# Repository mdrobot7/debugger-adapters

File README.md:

# debugger-adapters
Aliexpress STLINKv2 debugger to standard connector adapters

## Hardware
All part links are built into the KiCad parts, just generate the BOM from within KiCad and order. Miscellaneous parts are below.

- [Aliexpress STLINKv2](https://www.aliexpress.us/item/3256803389306042.html)
- [Cortex-debug Ribbon Cable](https://www.digikey.com/en/products/detail/cnc-tech/300-30-10-GR-0100F/5864892)
- [Pre-assembled Cortex-debug Cable](https://www.aliexpress.us/item/3256805917162371.html)

## Assembly
The ribbon cable IDC connectors for the Cortex-Debug adapter are quite difficult to get exactly right. If the wire goes in at slightly the wrong angle, the conductors will bridge or connect to the wrong pins. After each connector is put on, check each pin with a multimeter to make sure it's not bridged to anything it shouldn't be.

## Creating a Black Magic Probe
Black Magic Probe and Black Magic Debug are open-source SWD/JTAG debug projects for ARM Cortex microcontrollers. It gives you a bare GDB server and is platform-independent, so it will work on ARM Cortex microcontrollers regardless of brand or series.

To create a Black Magic Probe you need an existing debugger -- another Black Magic Probe, STLink (for ST-based debuggers), Atmel ICE (for Atmel chips), etc.

#### Resources
- [Black Magic Debug Website](https://black-magic.org/index.html)
- [Black Magic Debug Codeberg](https://codeberg.org/blackmagic-debug/blackmagic)
- [dfu-util Homepage](https://dfu-util.sourceforge.net/)
- [Zadig (Windows USB driver reinstaller)](https://zadig.akeo.ie/)

### Supported Hardware
- [Knockoff STLink v2 (Geehy MCU) - Aliexpress](https://www.aliexpress.us/item/3256803389306042.html)
- [Knockoff STLink v2 (STM32F101 MCU) - Aliexpress](https://www.aliexpress.us/item/3256803289344865.html)
- [STM32 "Blue Pill" (STM32F103C8T6) - Ebay](https://www.ebay.com/itm/292145343898)

### Wiring
Keep the SWD wires (between the BMP and the microcontroller) relatively short. SWD doesn't have a length spec, but under 30cm is a good rule of thumb. Slower baud rates will allow for longer lengths. It's recommended to extend the USB side instead of the SWD side.

### Reprogramming the BMP
The Black Magic Probe project switched to Meson in current releases, which makes installation a little harder on Windows. On Windows, your best move is load up a Linux VM using VirtualBox or something similar. You can try to get MSYS2 to work, but no guarantees. Builds and uploads on Windows may need [Zadig](https://zadig.akeo.ie/) to manually assign Windows drivers to your BMP, you want to assign it to **WinUSB**.

Instructions for Linux/Mac:

1. Install dependencies
   - Linux: `sudo apt install meson ninja gcc-arm-none-eabi gdb-multiarch binutils-arm-none-eabi dfu-util libhidapi-dev libftdi1-dev libusb-1.0-0-dev`
   - OSX: `brew install meson ninja arm-none-eabi-gcc arm-none-eabi-binutils arm-none-eabi-gdb dfu-util hidapi libftdi libusb`
3. `git clone https://codeberg.org/blackmagic-debug/blackmagic`
4. `cd` into the directory you cloned into
5. Set up the build: `meson setup build --reconfigure --cross-file cross-file/stlink.ini -Dtargets=cortexar,cortexm,sam,stm,nxp,ti -Dbmd_bootloader=true`
   - Which targets you choose are up to you and your use case. The ones shown above are a general recommendation. See [supported targets](https://black-magic.org/supported-targets.html) for others.
6. Build the binary and bootloader: `meson compile -C build; meson compile -C boot-bin`
7. Pull the metal shell off of your BMP-to-be by pulling it towards the USB port. Attach jumper wires to an existing BMP, and wire GND, VCC, SWDIO, and SWCLK to the pins/exposed pads on your BMP-to-be. You can wire it properly, or hold wires onto the pads until the next command is done.
8. Flash the bootloader
   - With an existing BMP: `arm-none-eabi-gdb -ex "tar ext [debugger device ID]" -ex "mon s" -ex "att 1" -ex "mon option erase" -ex "load" -batch build/blackmagic_stlink_bootloader.elf`
     - Find the debugger device ID in /dev. Use /dev/whatever for the following commands.
     - This worked on some targets (Geehy micros), but not all. I've received knockoff STLinks from AliExpress that have flash protections set up such that it doesn't flash. If so, grab a stock STLink and try the steps below.
   - With an existing STLink (credit to [this guide](https://microcontrollerelectronics.com/how-to-convert-an-stm32f103c8t6-into-a-black-magic-probe/)):
     - `sudo apt install openocd stlink-tools`
     - `sudo vim /usr/share/openocd/scripts/target/stm32f1x.cfg` and add `set CPUTAPID 0` below line 35. This disables CPU ID checking (we're flashing a counterfeit).
     - Plug in your existing STLinkv2 and connect it to your BMP-to-be.
     - `openocd -f interface/stlink-v2.cfg -f target/stm32f1x.cfg -c "init" -c "halt" -c "stm32f1x unlock 0" -c "shutdown" && st-flash erase && st-flash --flash=0x20000 --reset write build/blackmagic_stlink_bootloader.bin 0x8000000`
9. Plug your new BMP into your PC via USB, **unplug your existing debugger**.
10. Check that your new BMP shows up: `sudo dfu-util -l`. It should say "found DFU" with some device information.
11. Flash the BMP firmware: `sudo dfu-util -s 0x08002000:leave:force -D build/blackmagic_stlink_firmware.bin`

### Upgrading Your BMP
All you need to do is `git pull` the updated BMP firmware (or make any changes you need to), and rebuild. Plug it in via USB and rerun step 11 above. The bootloader handles reflashing the firmware over USB.

Black Magic Probe releases official binaries as well, so you can also download the `blackmagic-native` BIN file from the [Releases](https://codeberg.org/blackmagic-debug/blackmagic/releases) page and flash it over DFU. It covers a very similar set of debug targets and fits in the 128KB flash of our counterfeit STLinks.

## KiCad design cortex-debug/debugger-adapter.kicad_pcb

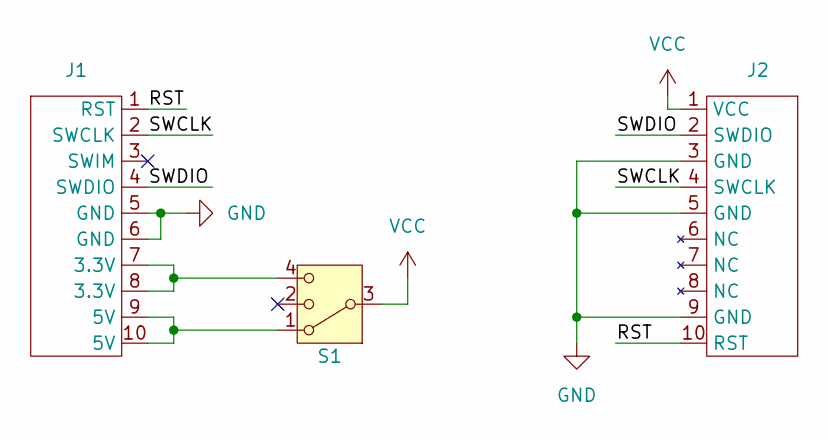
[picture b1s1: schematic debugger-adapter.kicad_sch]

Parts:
J1: STLINK_Header; Manufacturer Part Number SFH11-PBPC-D05-ST-BK; Digikey Part Number S9194-ND
J2: 0.05in_Ribbon_Header; Manufacturer Part Number 3240-10-00; Digikey Part Number 1175-1664-ND
S1: Slide_SP3T; Manufacturer Part Number CL-SB-13A-01T; Digikey Part Number 563-1326-1-ND

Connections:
/RST: J1.1 (RST), J2.10 (RST)
/SWCLK: J1.2 (SWCLK), J2.4 (SWCLK)
/SWDIO: J1.4 (SWDIO), J2.2 (SWDIO)
GND: J1.5 (GND), J1.6 (GND), J2.3 (GND), J2.5 (GND), J2.9 (GND)
unnamed: J1.7 (3.3V), J1.8 (3.3V), S1.4
unnamed: J1.9 (5V), J1.10 (5V), S1.1
VCC: J2.1 (VCC), S1.3

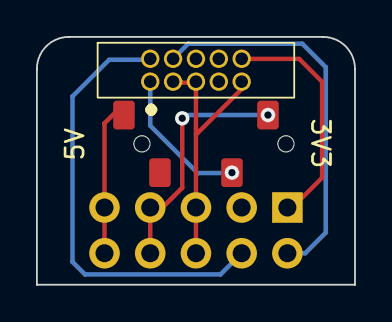
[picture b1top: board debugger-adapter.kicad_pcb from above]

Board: 2 copper layers, 17.7 x 13.8 mm, 3 parts (1 on the bottom side), 7 nets.

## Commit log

2024-02-16 Created cortex debug/swd debugger adapter
    I already made this in altium, this is the kicad version of it. Made all of the parts in their own common library so that making different adapters is easy in the future for stuff like JTAG, ST, AVR,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
2024-02-19 Added part links
2024-05-12 Docs update
2024-11-24 Add aliexpress pre-assembled cable to readme, export project files
2025-02-19 Update stlink connector footprint to a better part
    - No more jankily soldering in an IDC connector, found an actual connector that works
2025-09-22 Replace solder jumpers with selector switch
    I got annoyed that my debugger was set for the wrong
    voltage or set to provide power when I didn't want it to, so
    small revision to add a selector switch. Makes the board a little bigger
    but whatever.
2025-09-22 Fix symbol and footprint library paths
2026-04-14 Update build instructions to use meson and the new BMP repo
2026-05-02 Update README with new build and program instructions
    Ran into a bunch of issues building for and programming this latest
    round of knockoff BMPs. AliExpress sent me a new type of counterfeit
    "STM32F103" that had some sort of flash or boot protections enabled on
    it that didn't disable easily, it seems like the only thing that can do
    it is OpenOCD. Conveniently, I had a bunch of STLinks to work with :)
